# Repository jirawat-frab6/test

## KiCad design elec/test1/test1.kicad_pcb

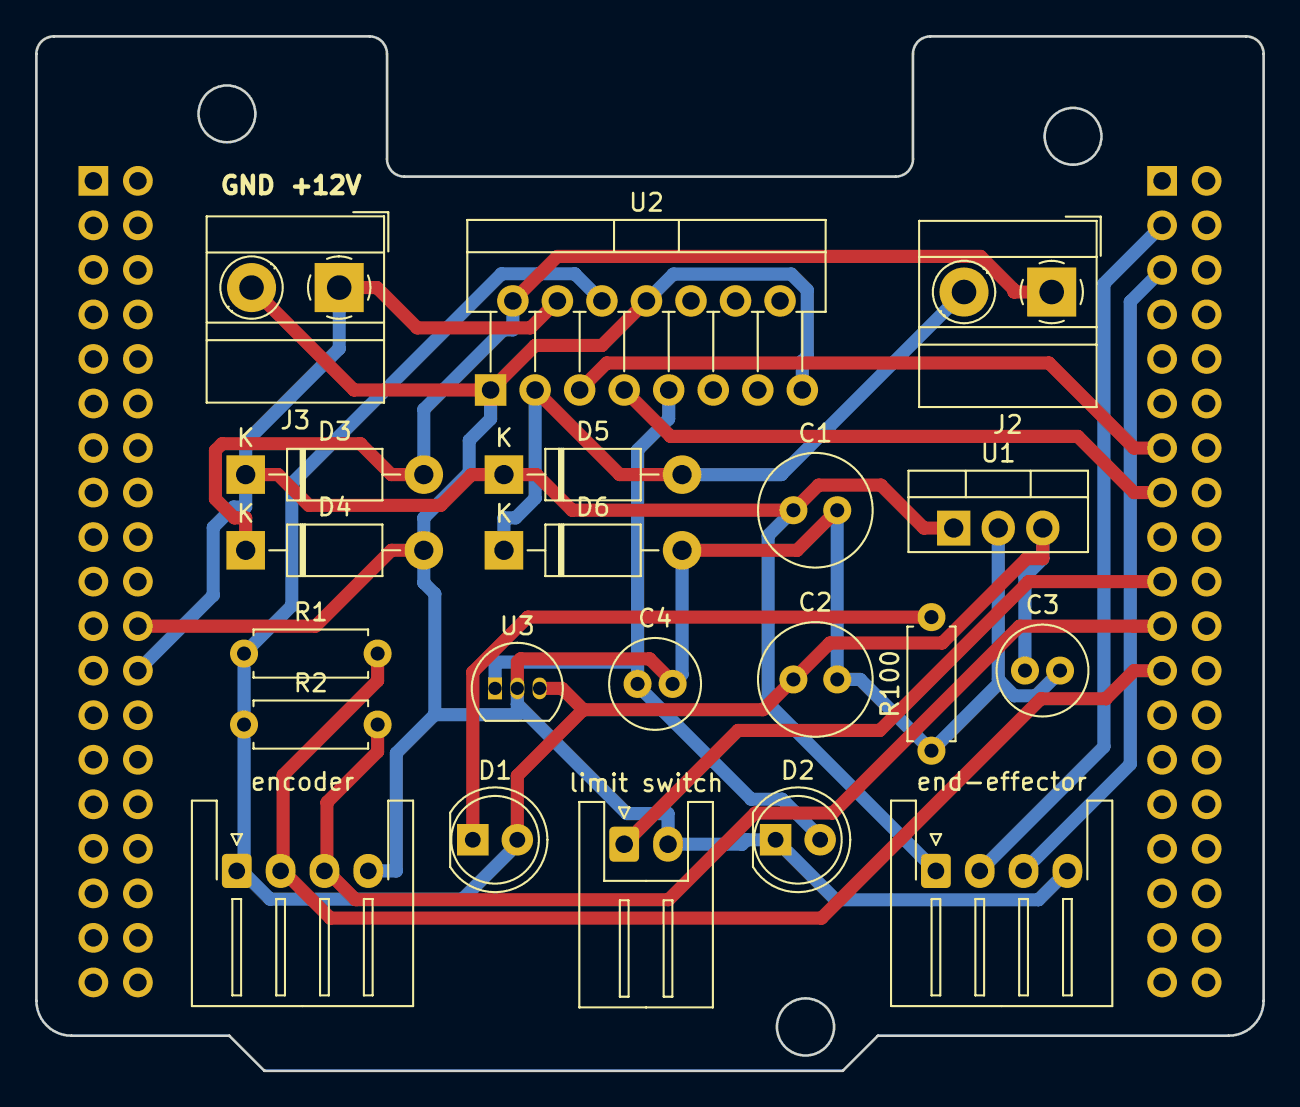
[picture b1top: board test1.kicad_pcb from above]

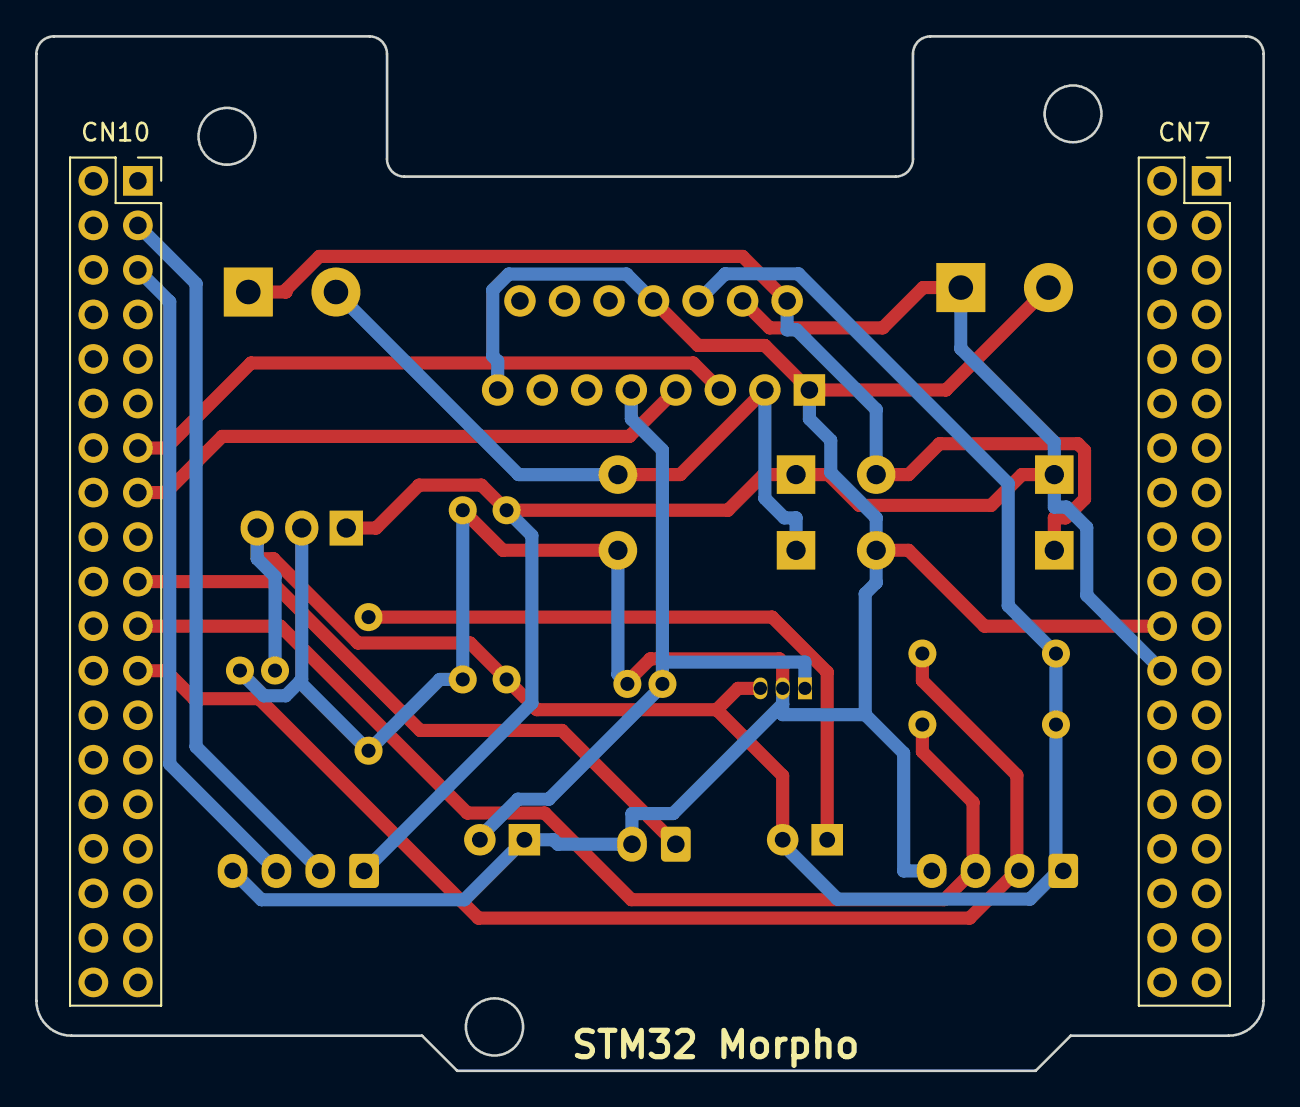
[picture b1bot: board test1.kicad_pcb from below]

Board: 2 copper layers, 70.0 x 59.0 mm, 23 parts (2 on the bottom side), 14 nets.

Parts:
C1, C2: C 3.3uf; C_Radial_D6.3mm_H11.0mm_P2.50mm
C3, C4: C 0.1uF; C_Radial_D5.0mm_H11.0mm_P2.00mm
CN7, CN10: Conn_02x19_Odd_Even; PinSocket_2x19_P2.54mm_Vertical
D1, D2: LED; LED_D5.0mm
D3, D4, D5, D6: 1N4007; D_DO-41_SOD81_P10.16mm_Horizontal
J2, J3: Screw_Terminal_01x02; TerminalBlock_MetzConnect_Type011_RT05502HBWC_1x02_P5.00mm_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
R1, R2: 1K; R_Axial_DIN0207_L6.3mm_D2.5mm_P7.62mm_Horizontal
R100: R; R_Axial_DIN0207_L6.3mm_D2.5mm_P7.62mm_Horizontal
U1: LM7805_TO220; TO-220-3_Vertical
U2: L298HN; TO-220-15_P2.54x2.54mm_StaggerOdd_Lead4.58mm_Vertical
U3: LP2950-3.3_TO92; TO-92_Inline
encoder: Conn_01x04; JST_XH_S4B-XH-A-1_1x04_P2.50mm_Horizontal
end-effector: Conn_01x04; JST_XH_S4B-XH-A-1_1x04_P2.50mm_Horizontal
limit switch: Conn_01x02; JST_XH_S2B-XH-A_1x02_P2.50mm_Horizontal

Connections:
+3V3: C4.1, D2.2, U2.9, U3.1
+5V: C2.1, C3.1, D1.2, R1.1, R2.1, U1.3, U2.6, U3.3, encoder.1
+12V: C1.1, CN7.24, D3.1, D5.1, J3.1, U1.1, U2.4, end-effector.1
/I2C_SCL: CN10.3, end-effector.2
/I2C_SDA: CN10.5, end-effector.3
/enc_a: CN10.23, R1.2, encoder.2
/enc_b: CN10.21, R2.2, encoder.3
/limit_switch: CN10.19, limit switch.1
/motor_pwm1: CN10.13, U2.5
/motor_pwm2: CN10.15, U2.7
GND: C1.2, C2.2, C3.2, C4.2, CN7.22, D2.1, D4.2, D6.2, J3.2, R100.1, U1.2, U2.1, U2.8, U2.15, U3.2, encoder.4, end-effector.4, limit switch.2
unnamed: D1.1, R100.2
unnamed: D3.2, D4.1, J2.1, U2.2
unnamed: D5.2, D6.1, J2.2, U2.3

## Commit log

2021-05-25 regualator
2021-05-25 regulator v1
2021-06-22 position control
    trapezoidal trajectory planning
2021-06-25 trajectory planning c++ version
2021-07-05 new_pin_config
2021-07-05 pcb_V1.0
2021-07-06 pcb_V1.1
